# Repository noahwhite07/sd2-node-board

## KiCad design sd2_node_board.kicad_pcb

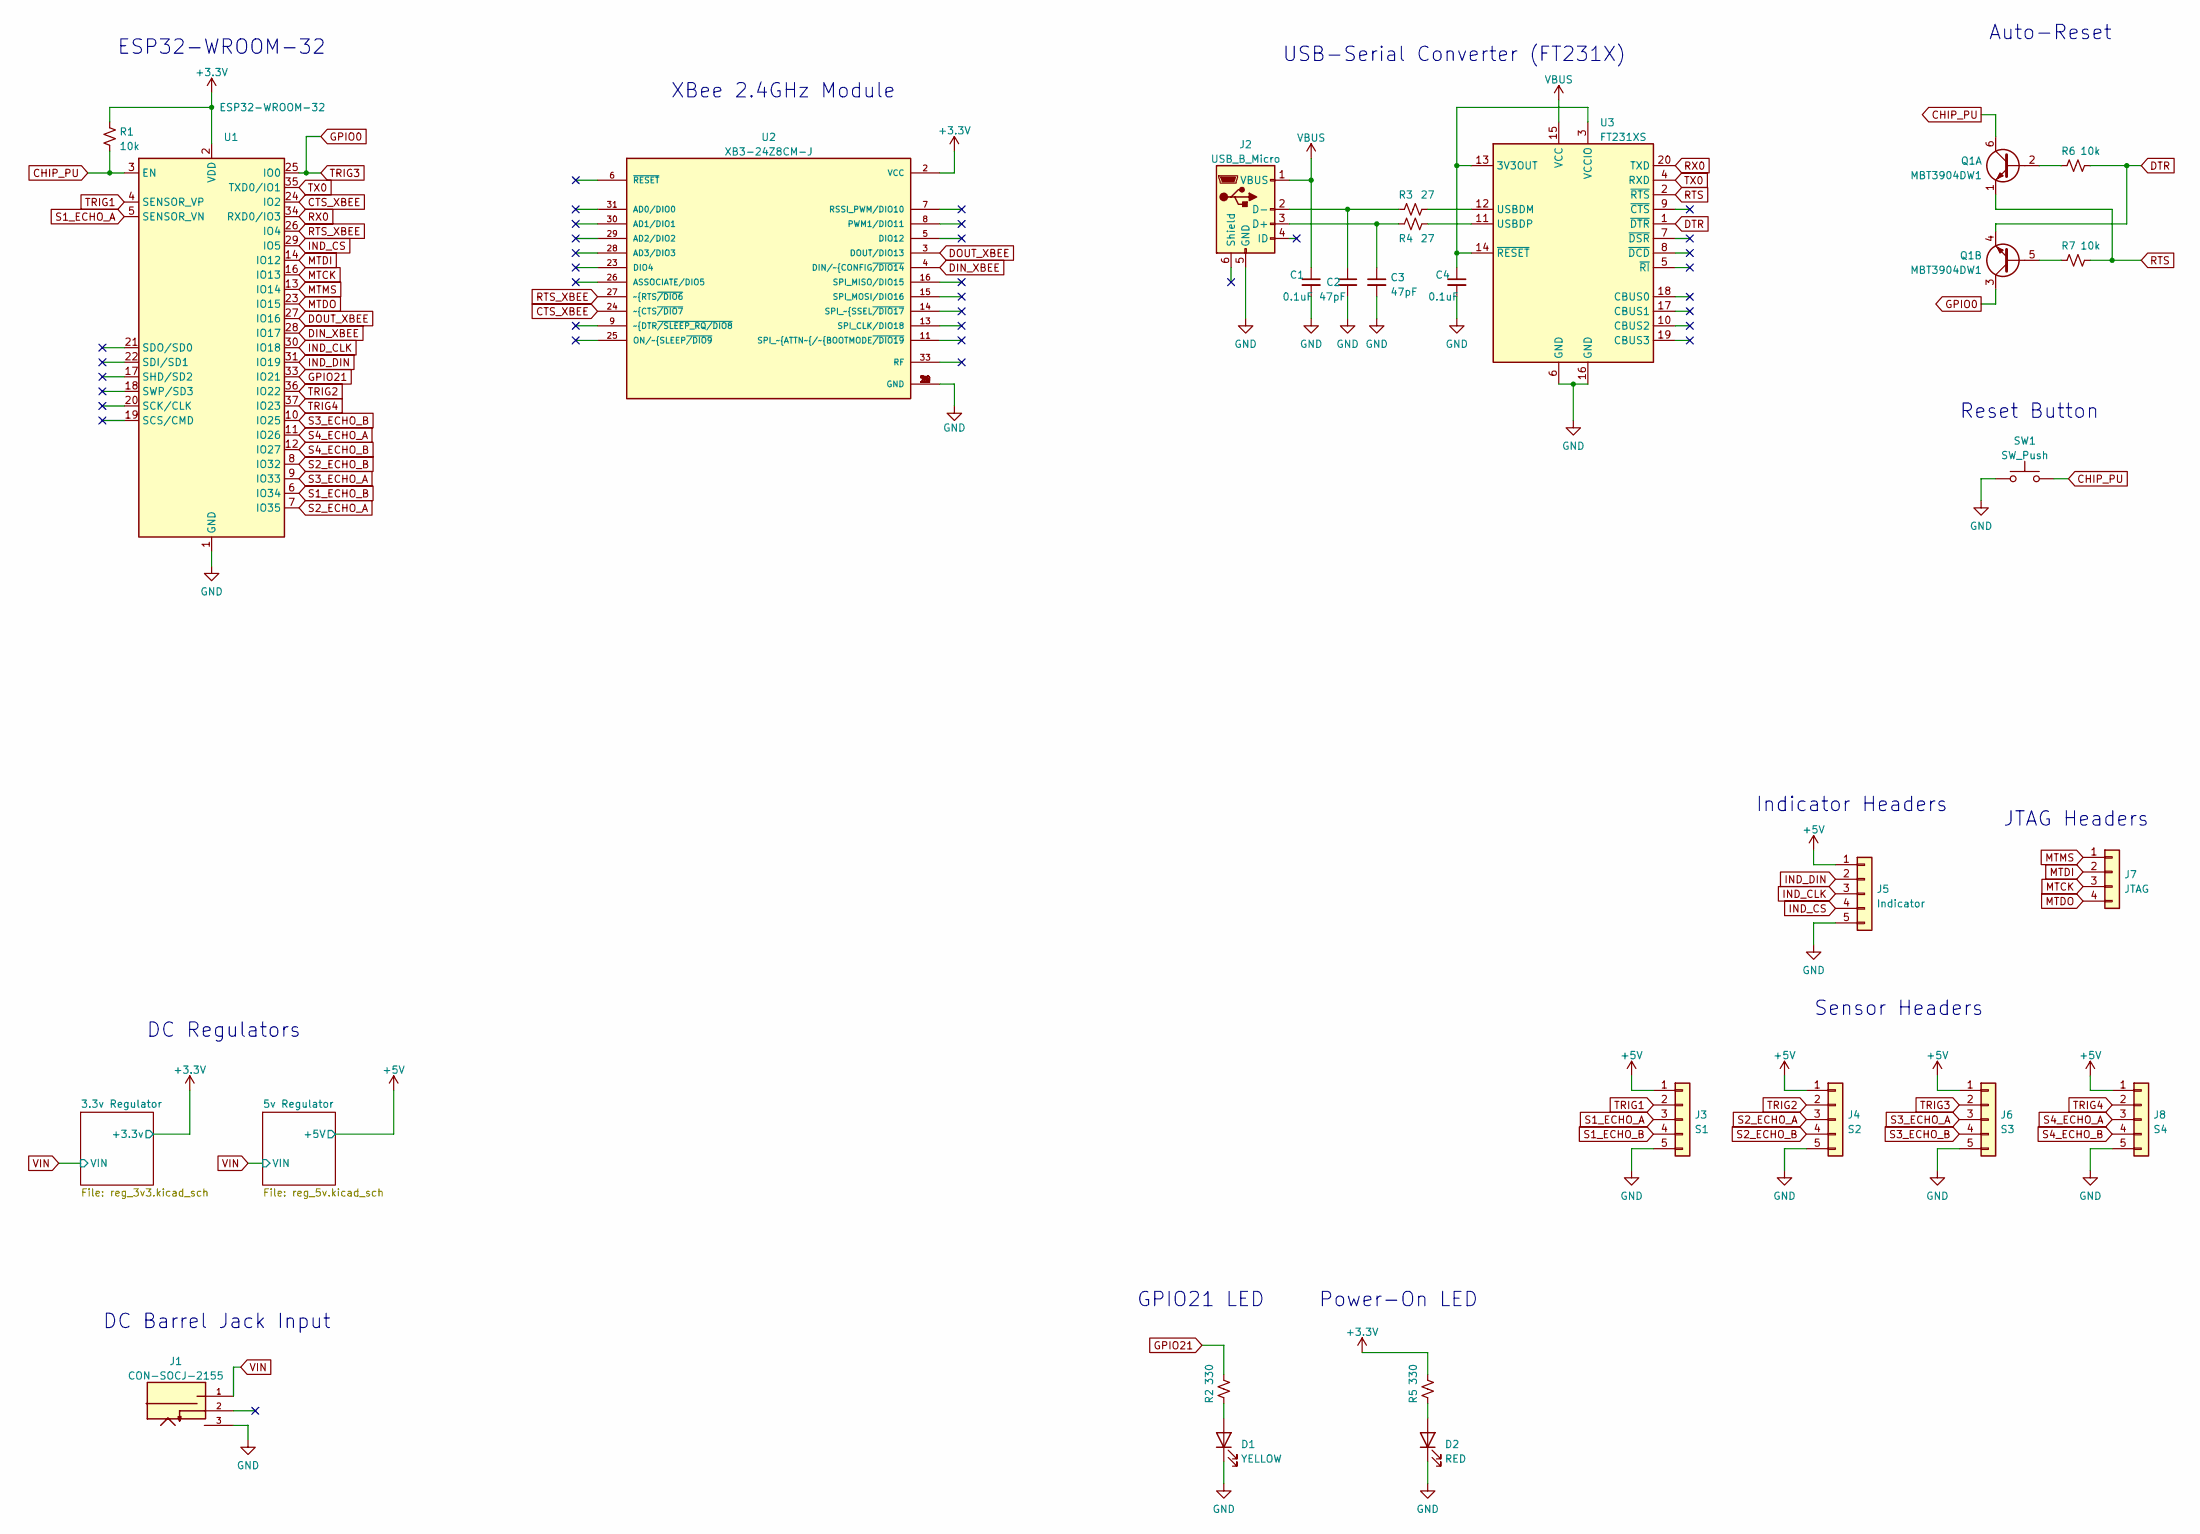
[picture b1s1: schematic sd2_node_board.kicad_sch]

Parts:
C1, C4: 0.1uF; C_0805_2012Metric_Pad1.18x1.45mm_HandSolder
C2, C3: 47pF; C_0805_2012Metric_Pad1.18x1.45mm_HandSolder
D1: YELLOW; LED_0805_2012Metric_Pad1.15x1.40mm_HandSolder
D2: RED; LED_0805_2012Metric_Pad1.15x1.40mm_HandSolder
J1: CON-SOCJ-2155; GRAVITECH_CON-SOCJ-2155; PARTREV NA
J2: USB_B_Micro; USB_Micro-B_GCT_USB3076-30-A
J3: S1; TerminalBlock_Phoenix_MKDS-1,5-5-5.08_1x05_P5.08mm_Horizont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
J4: S2; TerminalBlock_Phoenix_MKDS-1,5-5-5.08_1x05_P5.08mm_Horizont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
J5: Indicator; TerminalBlock_Phoenix_MKDS-1,5-5-5.08_1x05_P5.08mm_Horizont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
J6: S3; TerminalBlock_Phoenix_MKDS-1,5-5-5.08_1x05_P5.08mm_Horizont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
J7: JTAG; PinHeader_1x04_P2.54mm_Vertical
J8: S4; TerminalBlock_Phoenix_MKDS-1,5-5-5.08_1x05_P5.08mm_Horizont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
Q1: MBT3904DW1; SOT-363_SC-70-6_Handsoldering
R1, R6, R7: 10k; R_0805_2012Metric_Pad1.20x1.40mm_HandSolder
R2, R5: 330; R_0805_2012Metric_Pad1.20x1.40mm_HandSolder
R3, R4: 27; R_0805_2012Metric_Pad1.20x1.40mm_HandSolder
SW1: SW_Push; SW_Tactile_SPST_NO_Straight_CK_PTS636Sx25SMTRLFS
U1: ESP32-WROOM-32
U2: XB3-24Z8CM-J; XB3-24Z8UM-J; PARTREV N/A
U3: FT231XS; SSOP-20_3.9x8.7mm_P0.635mm

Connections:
+3.3V: R1.1, R5.1, U1.2 (VDD), U2.2 (VCC); also elsewhere on the board
+5V: J3.1, J4.1, J5.1, J6.1, J8.1; also elsewhere on the board
CHIP_PU: Q1.6 (C1), R1.2, SW1.2, U1.3 (EN)
CTS_XBEE: U1.24 (IO2), U2.24 (~CTS~{/DIO7)
DIN_XBEE: U1.28 (IO17), U2.4 (DIN/~CONFIG~{/DIO14)
DOUT_XBEE: U1.27 (IO16), U2.3 (DOUT/DIO13)
DTR: Q1.4 (E2), R6.1, U3.1 (~DTR)
GND: C1.2, C2.2, C3.2, C4.2, D1.1 (K), D2.1 (K), J1.3, J2.5 (GND), J3.5, J4.5, J5.5, J6.5, J8.5, SW1.1, U1.1 (GND), U1.15 (GND), U1.38 (GND), U1.39 (GND), U2.1 (GND), U2.10 (GND), U2.12 (GND), U2.21 (GND), U2.32 (GND), U2.34 (GND), U3.6 (GND), U3.16 (GND); also elsewhere on the board
GPIO21: R2.1, U1.33 (IO21)
IND_CLK: J5.3, U1.30 (IO18)
IND_CS: J5.4, U1.29 (IO5)
IND_DIN: J5.2, U1.31 (IO19)
MTCK: J7.3, U1.16 (IO13)
MTDI: J7.2, U1.14 (IO12)
MTDO: J7.4, U1.23 (IO15)
MTMS: J7.1, U1.13 (IO14)
unnamed: C2.1, J2.2 (D-), R3.2
unnamed: C3.1, J2.3 (D+), R4.2
unnamed: C4.1, U3.3 (VCCIO), U3.13 (3V3OUT), U3.14 (~RESET)
unnamed: D1.2 (A), R2.2
unnamed: D2.2 (A), R5.2
unnamed: Q1.2 (B1), R6.2
unnamed: Q1.5 (B2), R7.2
unnamed: R3.1, U3.12 (USBDM)
unnamed: R4.1, U3.11 (USBDP)
RTS: Q1.1 (E1), R7.1, U3.2 (~RTS)
RTS_XBEE: U1.26 (IO4), U2.27 (~RTS~{/DIO6)
RX0: U1.34 (RXD0/IO3), U3.20 (TXD)
S1_ECHO_A: J3.3, U1.5 (SENSOR_VN)
S1_ECHO_B: J3.4, U1.6 (IO34)
S2_ECHO_A: J4.3, U1.7 (IO35)
S2_ECHO_B: J4.4, U1.8 (IO32)
S3_ECHO_A: J6.3, U1.9 (IO33)
S3_ECHO_B: J6.4, U1.10 (IO25)
S4_ECHO_A: J8.3, U1.11 (IO26)
S4_ECHO_B: J8.4, U1.12 (IO27)
TRIG1: J3.2, U1.4 (SENSOR_VP)
TRIG2: J4.2, U1.36 (IO22)
TRIG3: J6.2, Q1.3 (C2), U1.25 (IO0)
TRIG4: J8.2, U1.37 (IO23)
TX0: U1.35 (TXD0/IO1), U3.4 (RXD)
VBUS: C1.1, J2.1 (VBUS), U3.15 (VCC)
VIN: J1.1; also elsewhere on the board

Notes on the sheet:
DC Barrel Jack Input
Reset Button
Power-On LED
JTAG Headers
Sensor Headers
XBee 2.4GHz Module
Auto-Reset
GPIO21 LED
USB-Serial Converter (FT231X)
Indicator Headers
DC Regulators
ESP32-WROOM-32

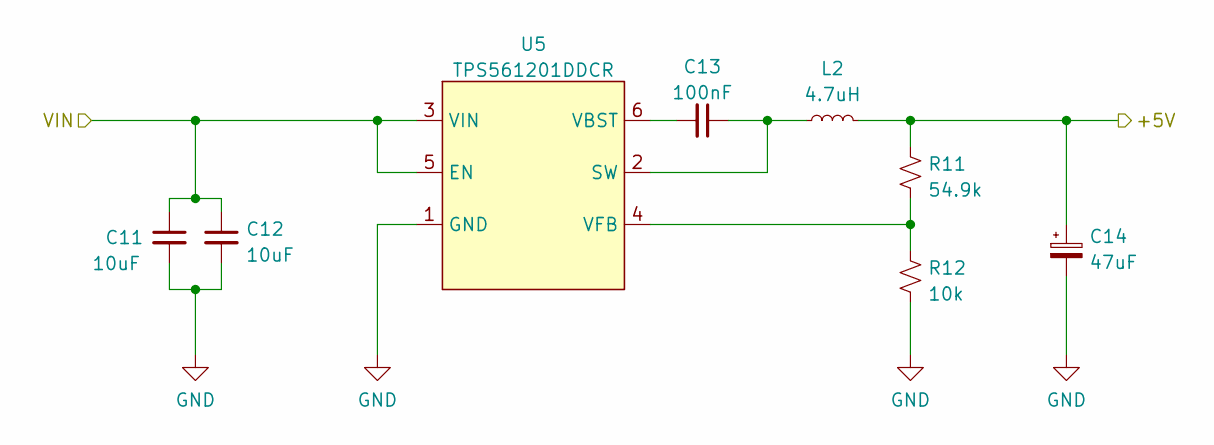
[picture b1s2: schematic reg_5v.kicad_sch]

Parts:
C11, C12: 10uF; C_0805_2012Metric_Pad1.18x1.45mm_HandSolder
C13: 100nF; C_0805_2012Metric_Pad1.18x1.45mm_HandSolder
C14: 47uF; C_0805_2012Metric_Pad1.18x1.45mm_HandSolder
L2: 4.7uH; L_0805_2012Metric_Pad1.15x1.40mm_HandSolder
R11: 54.9k; R_0805_2012Metric_Pad1.20x1.40mm_HandSolder
R12: 10k; R_0805_2012Metric_Pad1.20x1.40mm_HandSolder
U5: TPS561201DDCR; SOT-23-6

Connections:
+5V: C14.1, L2.2, R11.1; also elsewhere on the board
GND: C11.2, C12.2, C14.2, R12.2, U5.1 (GND); also elsewhere on the board
unnamed: C13.1, L2.1, U5.2 (SW)
unnamed: C13.2, U5.6 (VBST)
unnamed: R11.2, R12.1, U5.4 (VFB)
VIN: C11.1, C12.1, U5.3 (VIN), U5.5 (EN); also elsewhere on the board

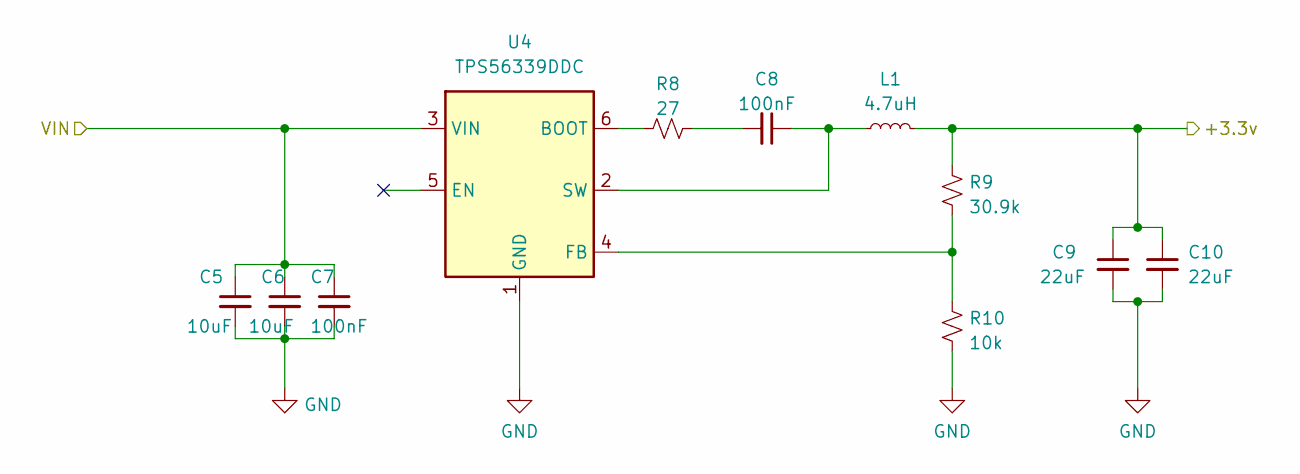
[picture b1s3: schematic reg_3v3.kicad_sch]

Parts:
C5, C6: 10uF; C_0805_2012Metric_Pad1.18x1.45mm_HandSolder
C7, C8: 100nF; C_0805_2012Metric_Pad1.18x1.45mm_HandSolder
C9, C10: 22uF; C_0805_2012Metric_Pad1.18x1.45mm_HandSolder
L1: 4.7uH; L_0805_2012Metric_Pad1.15x1.40mm_HandSolder
R8: 27; R_0805_2012Metric_Pad1.20x1.40mm_HandSolder
R9: 30.9k; R_0805_2012Metric_Pad1.20x1.40mm_HandSolder
R10: 10k; R_0805_2012Metric_Pad1.20x1.40mm_HandSolder
U4: TPS56339DDC; SOT-23-6

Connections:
+3.3V: C9.1, C10.1, L1.2, R9.1; also elsewhere on the board
GND: C5.2, C6.2, C7.2, C9.2, C10.2, R10.2, U4.1 (GND); also elsewhere on the board
unnamed: C8.1, L1.1, U4.2 (SW)
unnamed: C8.2, R8.1
unnamed: R8.2, U4.6 (BOOT)
unnamed: R9.2, R10.1, U4.4 (FB)
VIN: C5.1, C6.1, C7.1, U4.3 (VIN); also elsewhere on the board

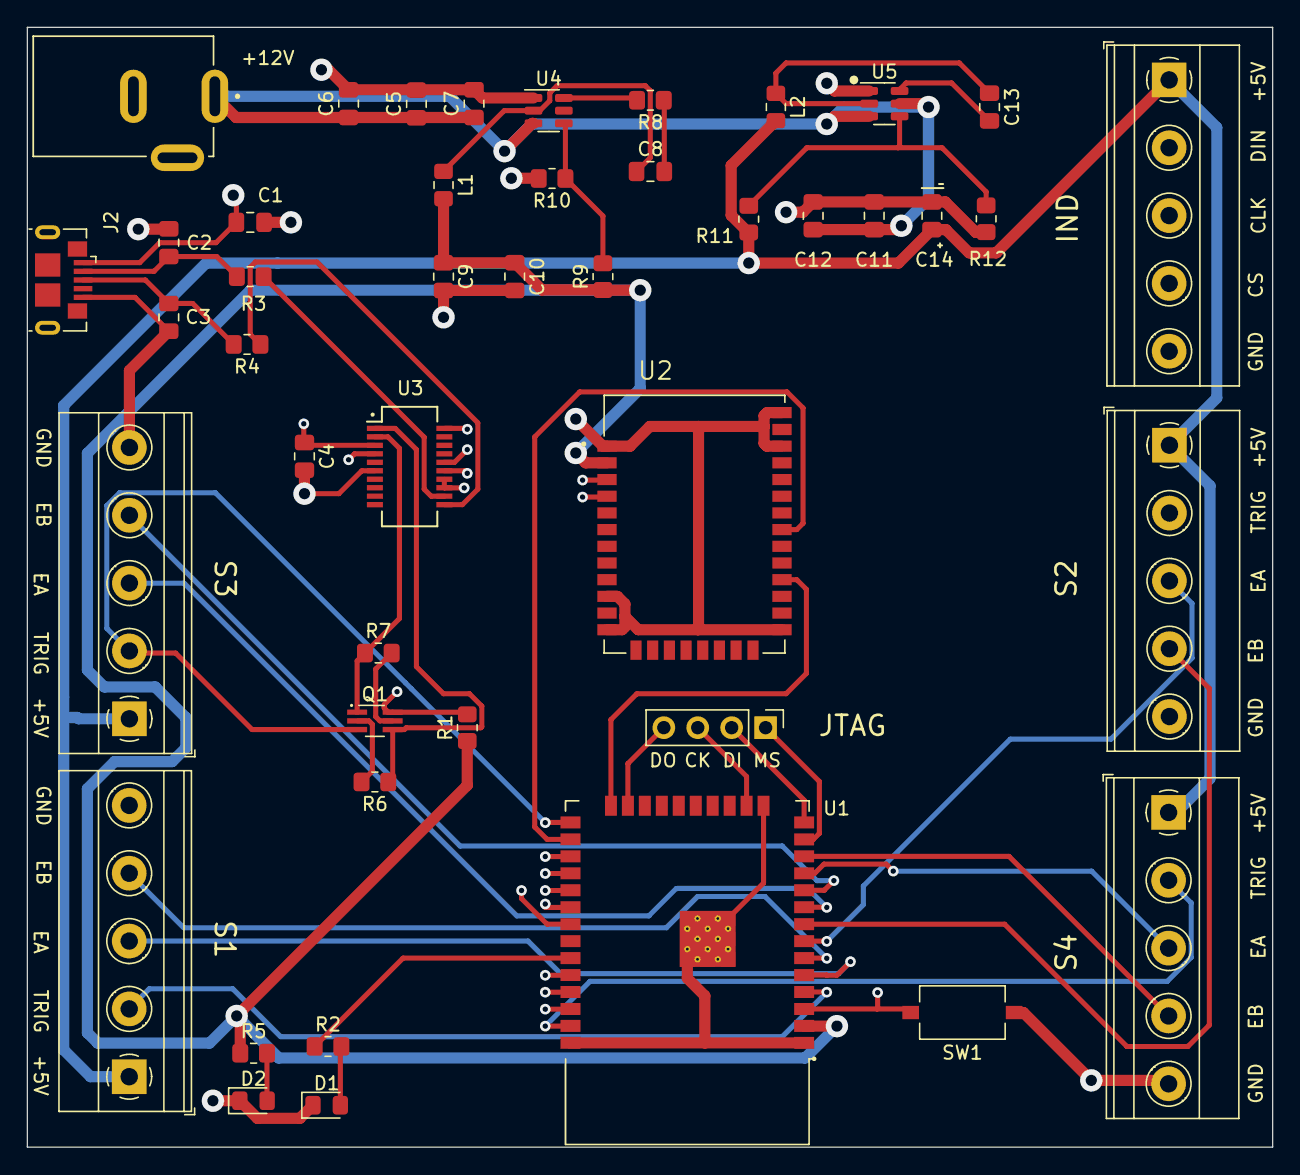
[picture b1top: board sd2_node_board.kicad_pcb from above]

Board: 4 copper layers, 93.3 x 83.9 mm, 45 parts (0 on the bottom side), 50 nets.

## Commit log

2023-06-23 Add components to schematic
2023-06-25 Finish schematic and start routing PCB
2023-06-25 Finish placing components
2023-06-25 Finish routing
2023-06-25 Finish silkscreen and fix thermal pad
2023-06-25 Fix silkscreen and generate Gerbers
